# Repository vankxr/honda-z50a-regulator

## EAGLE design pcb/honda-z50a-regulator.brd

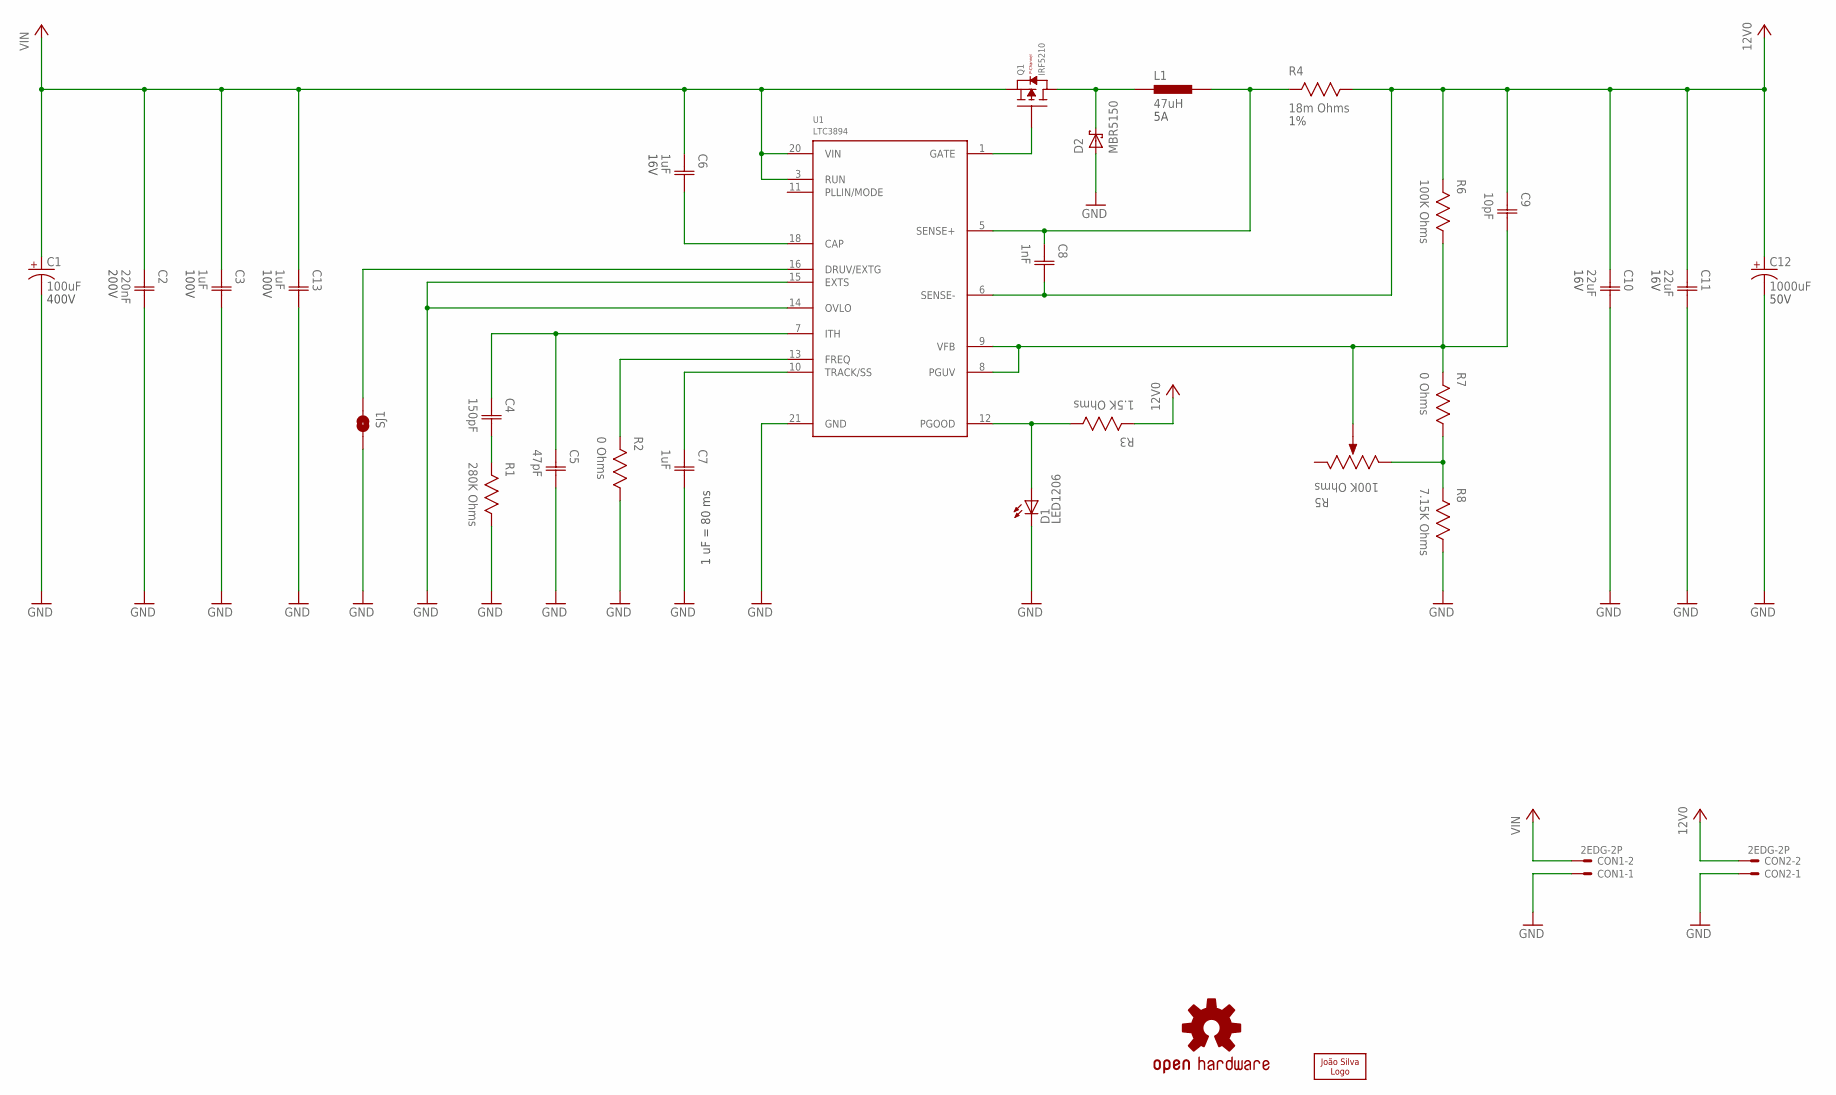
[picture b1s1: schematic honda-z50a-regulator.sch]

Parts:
C1: 100uF; EL-CAP-18MM; VOLTAGE 400V
C2: 220nF; CAP1206; VOLTAGE 200V
C3, C13: 1uF; CAP1206; VOLTAGE 100V
C4: 150pF; CAP0603
C5: 47pF; CAP0603
C6: 1uF; CAP0603; VOLTAGE 16V
C7: 1uF; CAP0603
C8: 1nF; CAP0603
C9: 10pF; CAP0603
C10, C11: 22uF; CAP1206; VOLTAGE 16V
C12: 1000uF; EL-CAP-13MM; VOLTAGE 50V
CON1, CON2: 2EDG-2P
D1: LED1206; 1206
D2: MBR5150; DO201AD
L1: 47uH; IND1365
LOGO1: OSHW-LOGOS; OSHW-LOGO-S
LOGO2: JS-5MM; JS_5MM
Q1: IRF5210; TO262-HS
R1: 280K Ohms; RES0603
R2, R7: 0 Ohms; RES0603
R3: 1.5K Ohms; RES0603
R4: 18m Ohms; RES2512; TOLERANCE 1%
R5: 100K Ohms; TRIMMER
R6: 100K Ohms; RES0603
R8: 7.15K Ohms; RES0603
SJ1: SJS; SJ_S
U1: LTC3894; MSOP20_HV_EP

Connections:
12V0: C8.2 (C2), C9.1 (C1), C10.1 (C1), C11.1 (C1), C12.+, CON2.P$2, R3.2, R4.1, R6.2, U1.6 (SENSE-)
CAP: C6.2 (C2), U1.18 (CAP)
DRUV: SJ1.1, U1.16 (DRUV/EXTG)
FREQ: R2.2, U1.13 (FREQ)
GATE: Q1.G, U1.1 (GATE)
GND: C1.-, C2.2 (C2), C3.2 (C2), C5.2 (C2), C7.2 (C2), C10.2 (C2), C11.2 (C2), C12.-, C13.2 (C2), CON1.P$1, CON2.P$1, D1.C, D2.A, R1.1, R2.1, R8.1, SJ1.2, U1.14 (OVLO), U1.15 (EXTS), U1.21 (GND)
ISENSE: C8.1 (C1), L1.2, R4.2, U1.5 (SENSE+)
ITH: C4.1 (C1), C5.1 (C1), U1.7 (ITH)
unnamed: R5.E (CW), R7.1, R8.2
unnamed: C4.2 (C2), R1.2
PGOOD: D1.A, R3.1, U1.12 (PGOOD)
SS: C7.1 (C1), U1.10 (TRACK/SS)
SW: D2.C, L1.1, Q1.D
VFB: C9.2 (C2), R5.S (WIPER), R6.1, R7.2, U1.8 (PGUV), U1.9 (VFB)
VIN: C1.+, C2.1 (C1), C3.1 (C1), C6.1 (C1), C13.1 (C1), CON1.P$2, Q1.S, U1.3 (RUN), U1.20 (VIN)

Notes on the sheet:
1 uF = 80 ms

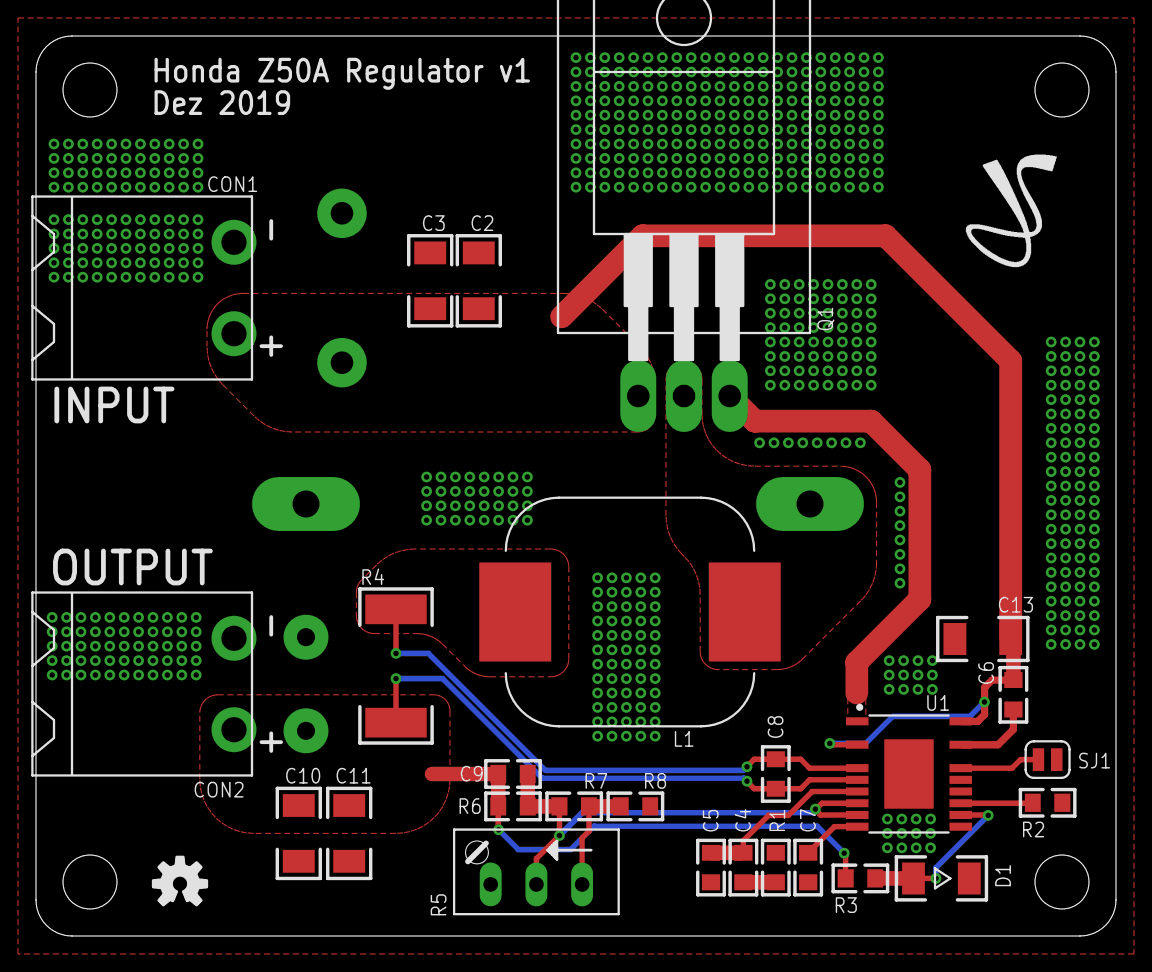
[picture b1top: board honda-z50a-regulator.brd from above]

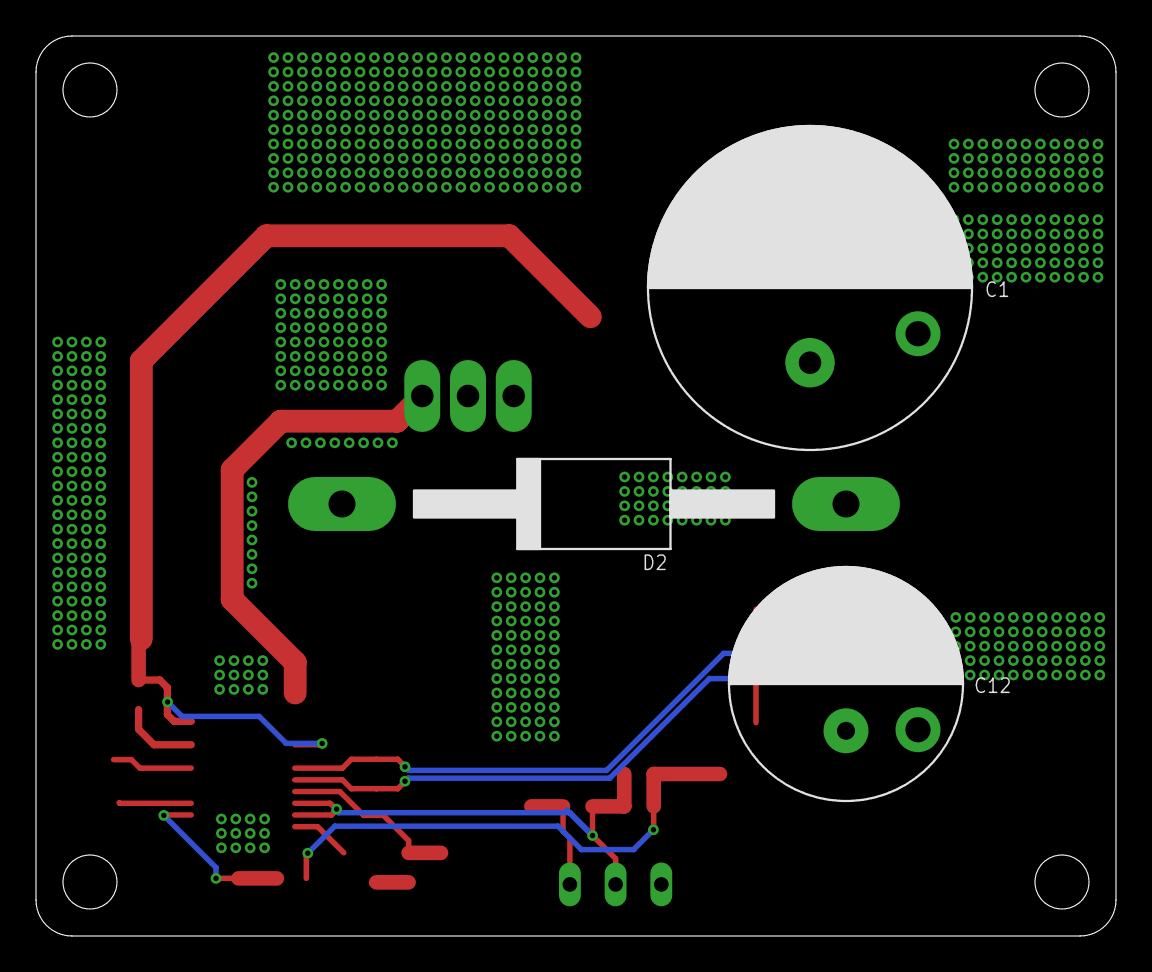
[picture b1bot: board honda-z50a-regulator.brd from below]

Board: 2 copper layers, 60.0 x 50.0 mm, 31 parts (3 on the bottom side), 15 nets.

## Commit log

2019-12-18 Add power part of schematic Route power part of the PCB
2019-12-19 Finish PCB Generate gerbers Export PDFs
2019-12-19 Remove useless script
2019-12-19 Update libraries
2019-12-30 Sync library updates
2020-03-17 Add motorbike user manual
